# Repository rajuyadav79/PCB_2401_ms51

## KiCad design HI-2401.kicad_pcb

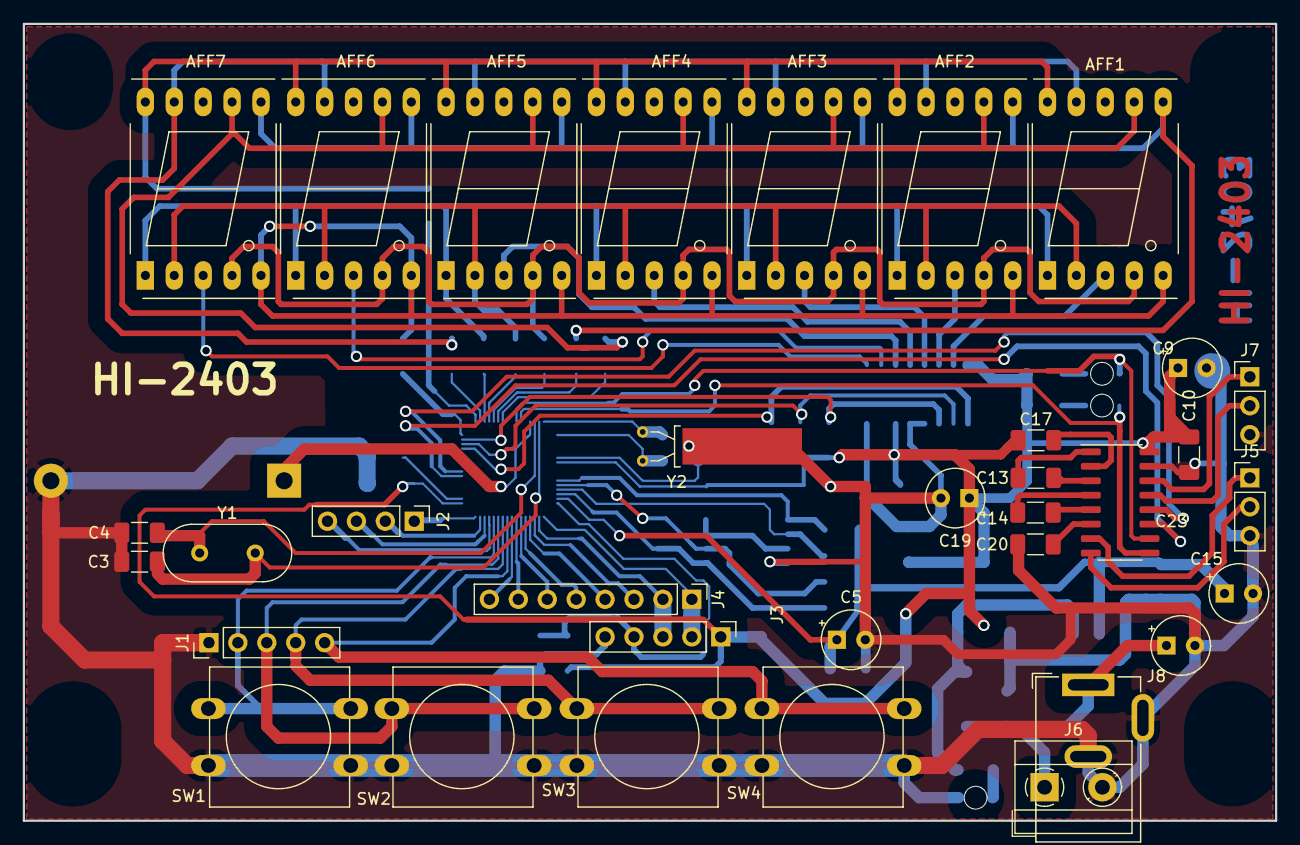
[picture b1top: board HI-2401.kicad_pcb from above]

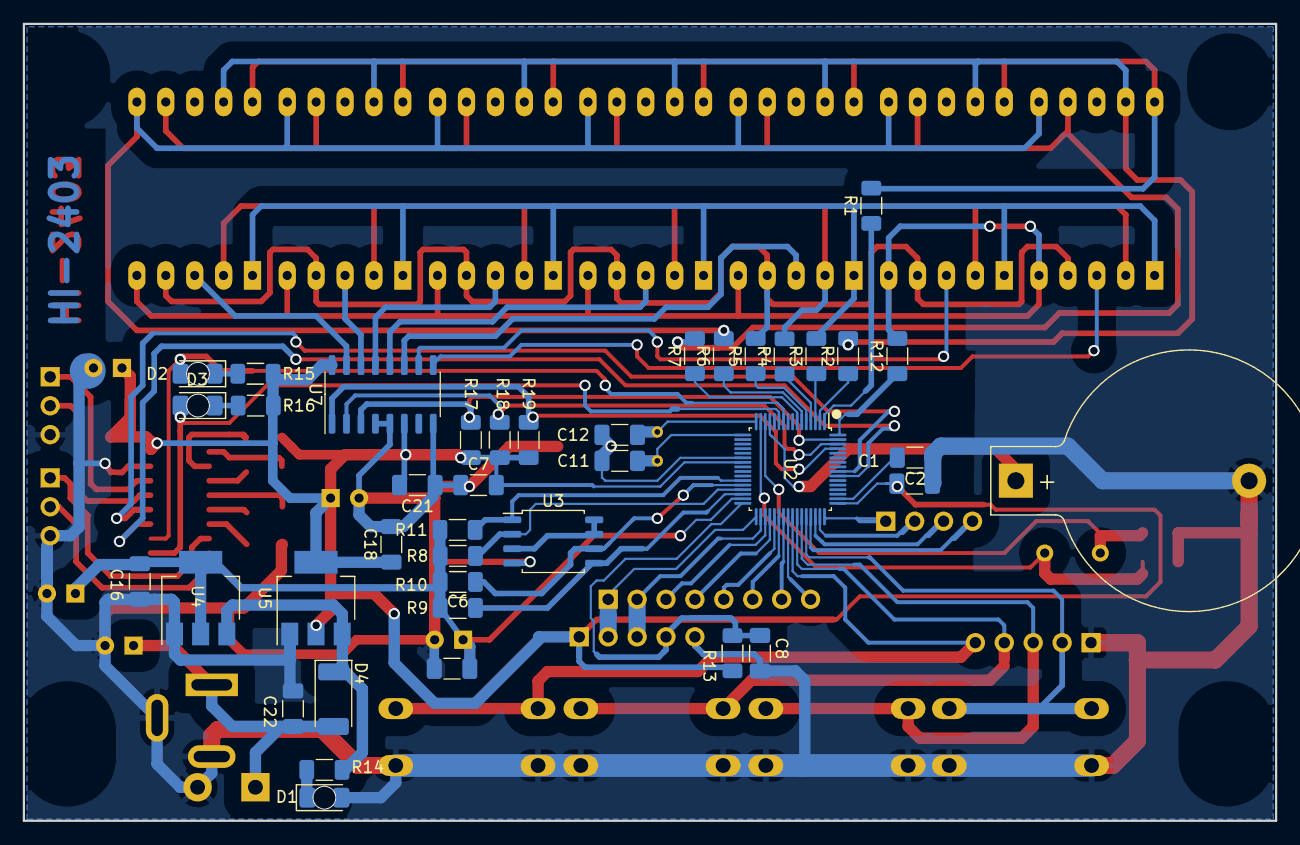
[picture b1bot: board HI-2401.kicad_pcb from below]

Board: 2 copper layers, 110.0 x 70.0 mm, 74 parts (40 on the bottom side), 75 nets.

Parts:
AFF1, AFF2, AFF3, AFF4, AFF5, AFF6, AFF7: LTS-6960HR; 7SegmentLED_LTS6760_LTS6780
BT1: Battery_Cell; BatteryHolder_Keystone_103_1x20mm
C1, C2, C6, C7, C8, C10, C13, C14, C16, C17, C18, C20, C21, C22: 104; C_1206_3216Metric_Pad1.33x1.80mm_HandSolder
C3, C4, C11, C12: 22PF; C_1206_3216Metric_Pad1.33x1.80mm_HandSolder
C5, C9, C15, C19: C_10MF/50V; CP_Radial_Tantal_D5.0mm_P2.50mm
C23: C_100MF/50V; CP_Radial_Tantal_D5.0mm_P2.50mm
D1, D2: LED RED; LED_1206_3216Metric_Pad1.42x1.75mm_HandSolder
D3: LED GREEN; LED_1206_3216Metric_Pad1.42x1.75mm_HandSolder
D4: SM4007; D_MELF
J1: Conn_01x05_Pin; PinHeader_1x05_P2.54mm_Vertical
J2: Conn_01x04; PinHeader_1x04_P2.54mm_Vertical
J3: Conn_01x05_Pin_prg; PinHeader_1x05_P2.54mm_Vertical
J4: Conn_01x08; PinHeader_1x08_P2.54mm_Vertical
J5, J7: Conn_01x03_Pin; PinHeader_1x03_P2.54mm_Vertical
J6: Conn_01x02_Pin; TerminalBlock_MetzConnect_Type101_RT01602HBWC_1x02_P5.08mm_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
J8: Conn_01x03; BarrelJack_GCT_DCJ200-10-A_Horizontal
R1, R2, R3, R4, R5, R6, R7, R12: 10E; R_1206_3216Metric_Pad1.30x1.75mm_HandSolder
R8, R9, R10, R11, R17, R18, R19: 10k; R_1206_3216Metric_Pad1.30x1.75mm_HandSolder
R13: 10K; R_1206_3216Metric_Pad1.30x1.75mm_HandSolder
R14, R15, R16: 3.3K; R_1206_3216Metric_Pad1.30x1.75mm_HandSolder
SW1, SW2, SW3, SW4: SW_DIP_x01; SW_PUSH-12mm
U2: M251SG6AE; LQFP-64_7x7mm_P0.4mm
U3: W25Q128JVS; SOIC-8_5.23x5.23mm_P1.27mm
U4: AP1117-33; SOT-223-3_TabPin2
U5: AP1117-50; SOT-223-3_TabPin2
U6: MAX232; SO-16_3.9x9.9mm_P1.27mm
U7: 74HC238; SO-16_3.9x9.9mm_P1.27mm
Y1: Crystal 16mhz; Crystal_HC49-U_Vertical
Y2: Crystal_GND2; Crystal_AT310_D3.0mm_L10.0mm_Horizontal_1EP_style1

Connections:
+3.3VDAC: C5.1, C6.2, C15.1, C16.1, R8.1, R9.1, R10.1, R11.1, U2.31 (VDDIO), U3.3 (IO2), U3.7 (IO3), U3.8 (VCC), U4.2 (VO)
+5V: C1.1, C7.2, C9.1, C10.2, C17.1, C18.1, C19.1, C21.2, J3.1, R13.1, R15.2, R16.2, R17.1, R18.1, R19.1, U2.23 (VDD), U2.49 (VSS), U5.2 (VO), U6.16 (VCC), U7.6 (E3), U7.16 (VCC)
/9vDC: D4.1 (K), R14.2, U4.3 (VI), U5.3 (VI)
/A: AFF1.7 (a), AFF2.7 (a), AFF3.7 (a), AFF4.7 (a), AFF5.7 (a), AFF6.7 (a), AFF7.7 (a), R7.2
/A0_HC238: R19.2, U2.61 (PB.10), U7.1 (A0)
/A1_HC238: R18.2, U2.62 (PB.9), U7.2 (A1)
/A2_HC238: R17.2, U2.63 (PB.8), U7.3 (A2)
/B: AFF1.6 (b), AFF2.6 (b), AFF3.6 (b), AFF4.6 (b), AFF5.6 (b), AFF6.6 (b), AFF7.6 (b), R6.2
/C: AFF1.4 (c), AFF2.4 (c), AFF3.4 (c), AFF4.4 (c), AFF5.4 (c), AFF6.4 (c), AFF7.4 (c), R5.2
/D: AFF1.2 (d), AFF2.2 (d), AFF3.2 (d), AFF4.2 (d), AFF5.2 (d), AFF6.2 (d), AFF7.2 (d), R4.2
/DP: AFF1.5 (DP), AFF2.5 (DP), AFF3.5 (DP), AFF4.5 (DP), AFF5.5 (DP), AFF6.5 (DP), AFF7.5 (DP), R12.2
/E: AFF1.1 (e), AFF2.1 (e), AFF3.1 (e), AFF4.1 (e), AFF5.1 (e), AFF6.1 (e), AFF7.1 (e), R3.2
/F: AFF1.9 (f), AFF2.9 (f), AFF3.9 (f), AFF4.9 (f), AFF5.9 (f), AFF6.9 (f), AFF7.9 (f), R2.2
/G: AFF1.10 (g), AFF2.10 (g), AFF3.10 (g), AFF4.10 (g), AFF5.10 (g), AFF6.10 (g), AFF7.10 (g), R1.2
/ICE_CLK: J3.3, J4.2, U2.34 (PF.1)
/ICE_DATA: J3.2, J4.1, U2.33 (PF.0)
/KEY1: J1.2, SW1.2, U2.44 (PD.0)
/KEY2: J1.3, SW2.2, U2.43 (PD.1)
/KEY3: J1.4, SW3.2, U2.42 (PD.2)
/KEY4: J1.5, SW4.2, U2.41 (PD.3)
/RST: C8.1, J3.4, R13.2, U2.32 (RESET)
/SEG1: AFF1.3 (C.A.), U7.15 (Y0)
/SEG2: AFF2.3 (C.A.), U7.14 (Y1)
/SEG3: AFF3.3 (C.A.), U7.13 (Y2)
/SEG4: AFF4.3 (C.A.), U7.12 (Y3)
/SEG5: AFF5.3 (C.A.), U7.11 (Y4)
/SEG6: AFF6.3 (C.A.), U7.10 (Y5)
/SEG7: AFF7.3 (C.A.), U7.9 (Y6)
/U0RXD: U2.56 (PB.14), U6.12 (R1OUT)
/U0TXD: U2.55 (PB.15), U6.11 (T1IN)
/W_CLK: R10.2, U2.28 (PA.2), U3.6 (CLK)
/W_CS: R11.2, U2.27 (PA.3), U3.1 (~CS)
/W_DI: R9.2, U2.30 (PA.0), U3.5 (DI(IO0))
/W_DO: R8.2, U2.29 (PA.1), U3.2 (DO(IO1))
/XLIN: C12.2, U2.16 (PF.3), Y2.2
/XLOUT: C11.1, U2.17 (PF.2), Y2.1
/rxd: J5.2, U6.8 (R2IN)
/rxd1: J7.2, U6.13 (R1IN)
/rxd_TTL: D3.2 (A), U2.11 (PA.8), U6.9 (R2OUT)
/txd: J5.1, U6.7 (T2OUT)
/txd1: J7.1, U6.14 (T1OUT)
/txd_TTL: D2.2 (A), U2.10 (PA.9), U6.10 (T2IN)
GND: BT1.2 (-), C1.2, C2.1, C3.2, C4.2, C5.2, C6.1, C7.1, C8.2, C9.2, C10.1, C11.2, C12.1, C15.2, C16.2, C18.2, C19.2, C20.1, C21.1, C22.1, C23.2, D1.2 (A), J1.1, J3.5, J5.3, J6.2, J7.3, J8.2, J8.3, SW1.1, SW2.1, SW3.1, SW4.1, U2.22 (VSS), U3.4 (GND), U4.1 (GND), U5.1 (GND), U6.15 (GND), U7.4 (~E1), U7.5 (~E2), U7.8 (GND), Y2.3
unnamed: BT1.1 (+), U2.13 (VBAT)
unnamed: D1.1 (K), R14.1
unnamed: D2.1 (K), R15.1
unnamed: D3.1 (K), R16.1
unnamed: C22.2, C23.1, D4.2 (A), J6.1, J8.1
unnamed: J2.1, U2.48 (PA.15)
unnamed: J2.2, U2.47 (PA.14)
unnamed: J2.3, U2.46 (PA.13)
unnamed: J2.4, U2.45 (PA.12)
unnamed: J4.3, U2.35 (PC.5)
unnamed: J4.4, U2.36 (PC.4)
unnamed: J4.5, U2.37 (PC.3)
unnamed: J4.6, U2.38 (PC.2)
unnamed: J4.7, U2.39 (PC.1)
unnamed: J4.8, U2.40 (PC.0)
unnamed: C2.2, U2.50 (LDO_CAP)
unnamed: R7.1, U2.7 (PB.0)
unnamed: R6.1, U2.6 (PB.1)
unnamed: R5.1, U2.5 (PB.2)
unnamed: R4.1, U2.4 (PB.3)
unnamed: R3.1, U2.3 (PB.4)
unnamed: R2.1, U2.2 (PB.5)
unnamed: R1.1, U2.1 (PB.6)
unnamed: R12.1, U2.64 (PB.7)
unnamed: C3.1, U2.15 (PF.4), Y1.2
unnamed: C4.1, U2.14 (PF.5), Y1.1
unnamed: C13.1, U6.1 (C1+)
unnamed: C13.2, U6.3 (C1-)
unnamed: C14.2, U6.4 (C2+)
unnamed: C14.1, U6.5 (C2-)
unnamed: C17.2, U6.2 (VS+)
unnamed: C20.2, U6.6 (VS-)

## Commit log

2024-04-19 ADD all file int
